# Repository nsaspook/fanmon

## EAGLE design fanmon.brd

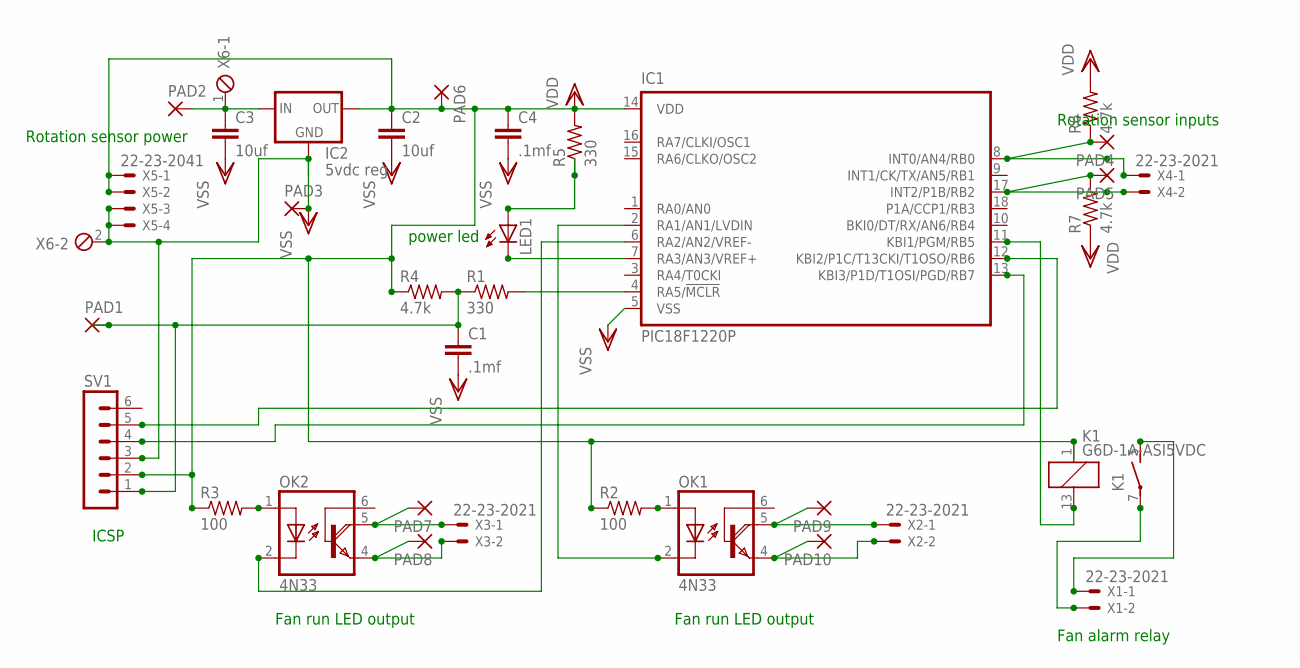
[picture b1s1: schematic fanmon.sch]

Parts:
C1, C4: .1mf; C5B2.5
C2, C3: 10uf; C5B2.5
IC1: PIC18F1220P; DIL18
IC2: 5vdc reg; 78XXL
K1: G6D-1A-ASI5VDC; G6D
LED1: LED5MM
OK1, OK2: 4N33; DIL06
PAD1, PAD2, PAD3, PAD4, PAD5, PAD6, PAD7, PAD8, PAD9, PAD10: 1,6/0,8
R1, R5: 330; 0204V
R2, R3: 100; 0204V
R4, R6, R7: 4.7k; 0204V
SV1: MA06-1
X1, X2, X3, X4: 22-23-2021
X5: 22-23-2041
X6: MPT2; 2POL254

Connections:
unnamed: IC1.4 (RA5/!MCLR), R1.2
unnamed: OK1.1 (A), R2.2
unnamed: OK2.1 (A), R3.2
unnamed: C1.1, PAD1.1, R1.1, R4.2, SV1.1
unnamed: IC1.8 (INT0/AN4/RB0), PAD4.1, R6.1, X4.1
unnamed: C3.1, IC2.IN, PAD2.1, X6.1
unnamed: IC1.17 (INT2/P1B/RB2), PAD5.1, R7.2, X4.2
unnamed: IC1.2 (RA1/AN1/LVDIN), OK1.2 (C)
unnamed: IC1.6 (RA2/AN2/VREF-), OK2.2 (C)
unnamed: OK2.5 (COL), PAD7.1, X3.1
unnamed: OK2.4 (E), PAD8.1, X3.2
unnamed: OK1.5 (COL), PAD9.1, X2.1
unnamed: OK1.4 (E), PAD10.1, X2.2
unnamed: LED1.A, R5.1
unnamed: IC1.7 (RA3/AN3/VREF+), LED1.K (C)
unnamed: IC1.11 (KBI1/PGM/RB5), K1.13 (2)
unnamed: K1.7, X1.2
unnamed: K1.5 (S), X1.1
unnamed: IC1.13 (KBI3/P1D/T1OSI/PGD/RB7), SV1.4
unnamed: IC1.12 (KBI2/P1C/T13CKI/T1OSO/RB6), SV1.5
VDD: C2.1, C4.1, IC1.14 (VDD), IC2.OUT, K1.1, PAD6.1, R2.1, R3.1, R4.1, R5.2, R6.2, R7.1, SV1.2, X5.1, X5.2
VSS: C1.2, C2.2, C3.2, C4.2, IC1.5 (VSS), IC2.GND, PAD3.1, SV1.3, X5.3, X5.4, X6.2

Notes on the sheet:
Rotation sensor inputs
Rotation sensor power
Fan run LED output
Fan alarm relay
power led
ICSP

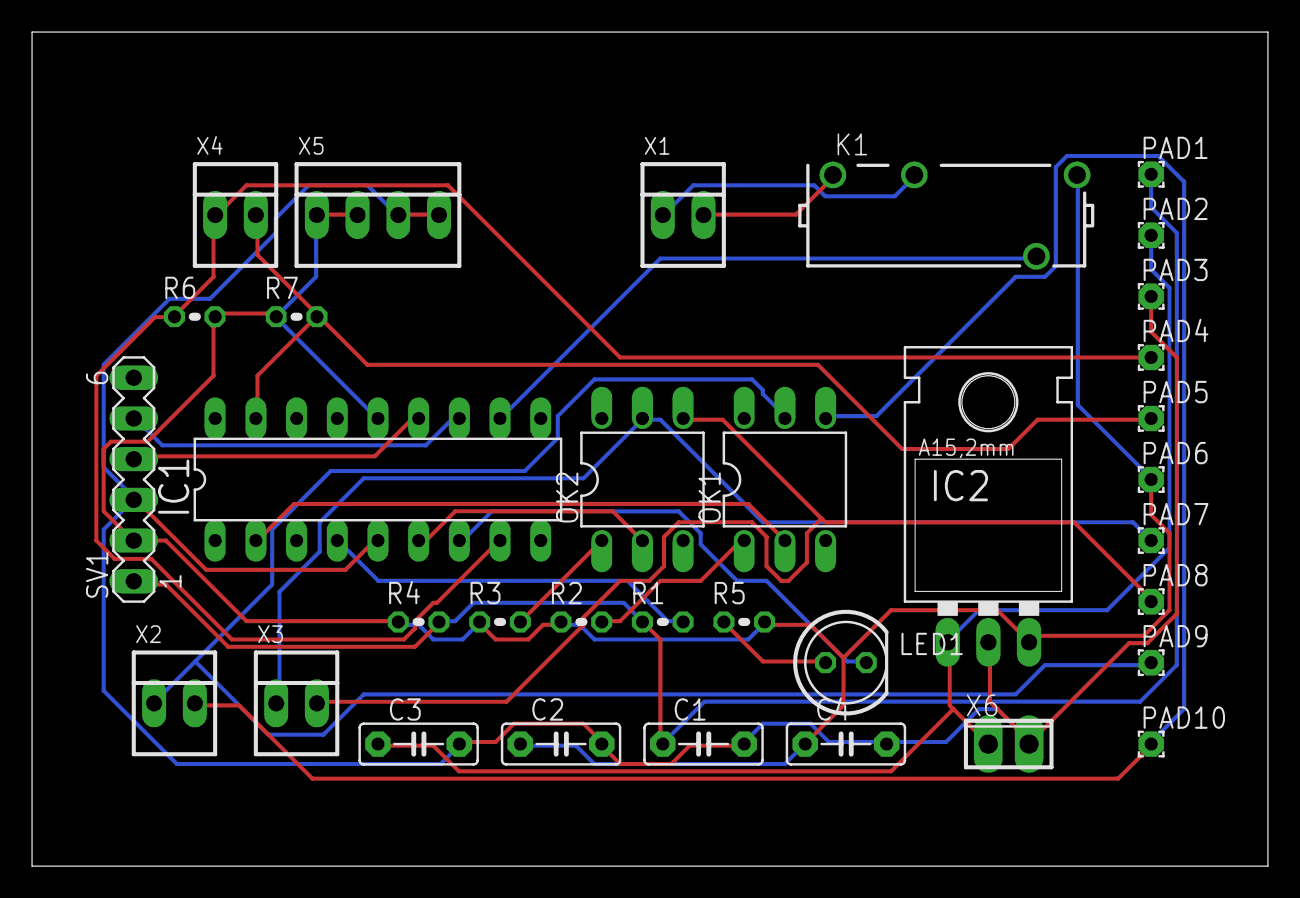
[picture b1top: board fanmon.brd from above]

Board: 2 copper layers, 77.1 x 52.1 mm, 35 parts (0 on the bottom side), 22 nets.

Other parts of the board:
DRILEGEND: DRILEGEND

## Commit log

2016-03-17 move files
